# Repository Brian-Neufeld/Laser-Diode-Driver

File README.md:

# Laser-Diode-Driver

A constant current laser diode driver with a maximum supply current of 500 mA.

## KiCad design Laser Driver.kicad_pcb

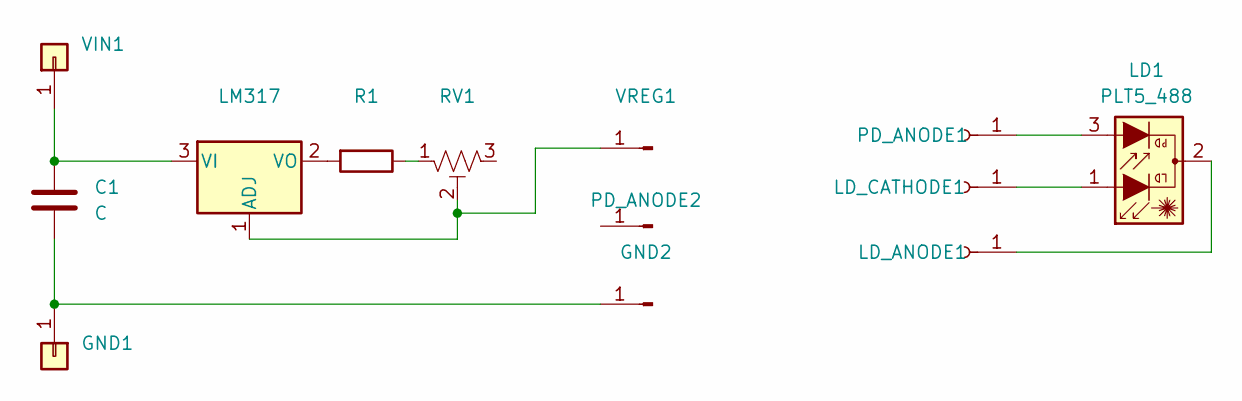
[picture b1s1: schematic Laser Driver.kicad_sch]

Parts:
C1: C; C_0805_2012Metric_Pad1.18x1.45mm_HandSolder
GND1: Conn_01x01; PinHeader_1x01_P2.54mm_Vertical
GND2: Conn_01x01_Pin; PinHeader_1x01_P2.54mm_Horizontal
LD1: PLT5_488; LaserDiode_TO56-3
LD_ANODE1: Conn_01x01_Socket; PinSocket_1x01_P2.54mm_Vertical
LD_CATHODE1: Conn_01x01_Socket; PinSocket_1x01_P2.54mm_Vertical
LM317: LM317_TO-220; SOT-223
PD_ANODE1: Conn_01x01_Socket; PinSocket_1x01_P2.54mm_Vertical
PD_ANODE2: Conn_01x01_Pin; PinHeader_1x01_P2.54mm_Horizontal
R1: R; R_0805_2012Metric_Pad1.20x1.40mm_HandSolder
RV1: R_Potentiometer_Trim_US; Potentiometer_Bourns_3006P_Horizontal
VIN1: Conn_01x01; PinHeader_1x01_P2.54mm_Vertical
VREG1: Conn_01x01_Pin; PinHeader_1x01_P2.54mm_Horizontal

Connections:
unnamed: C1.2, GND1.1, GND2.1
unnamed: LD1.2, LD_ANODE1.1
unnamed: LD1.1, LD_CATHODE1.1
unnamed: LM317.1 (ADJ), RV1.2, VREG1.1
unnamed: C1.1, LM317.3 (VI), VIN1.1
unnamed: LM317.2 (VO), R1.2
unnamed: LD1.3, PD_ANODE1.1
unnamed: R1.1, RV1.1

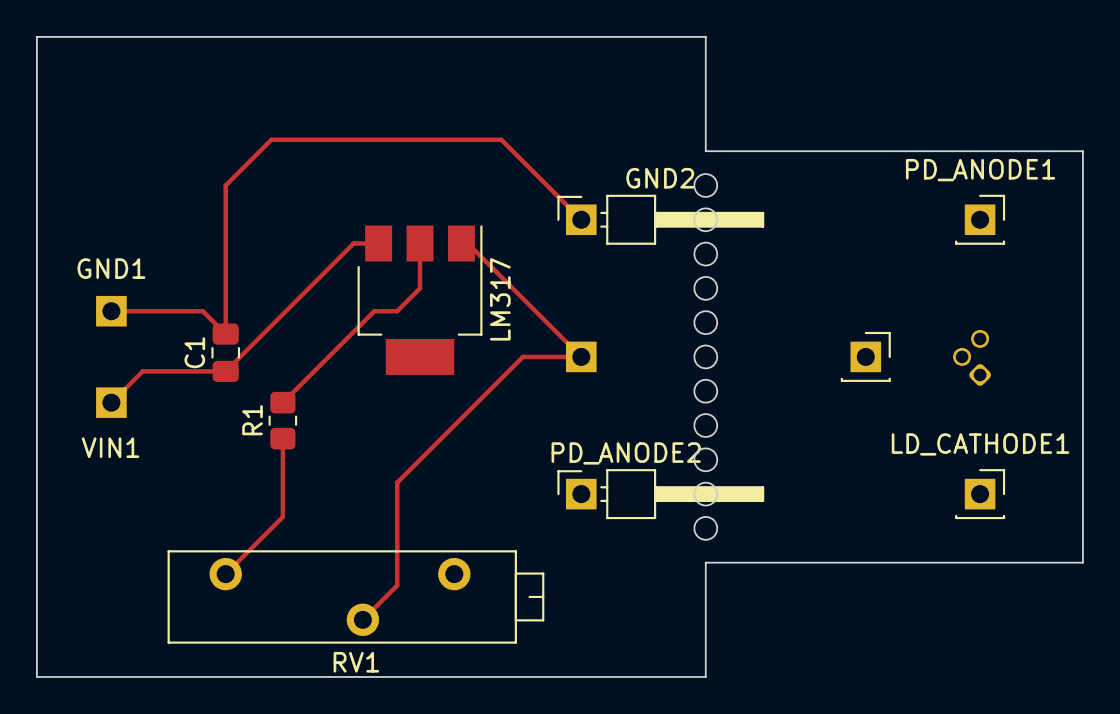
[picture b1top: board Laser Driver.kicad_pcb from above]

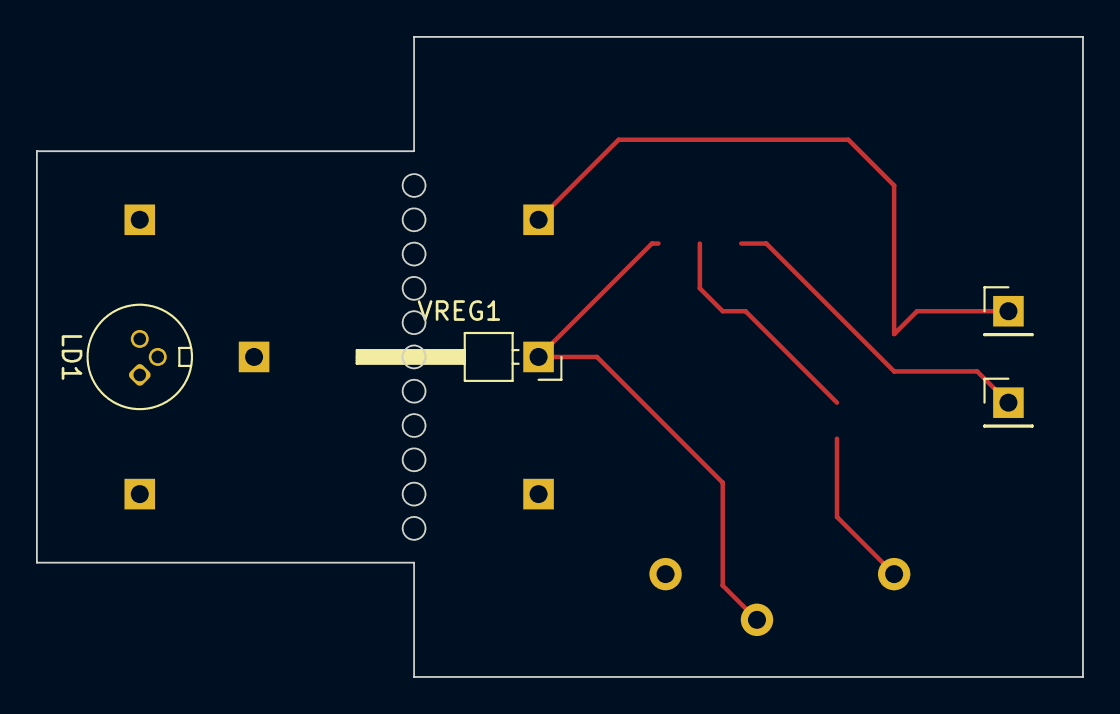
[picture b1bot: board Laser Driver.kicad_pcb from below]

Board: 2 copper layers, 58.1 x 35.6 mm, 13 parts (4 on the bottom side), 8 nets.
